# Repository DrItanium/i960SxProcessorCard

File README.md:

A 4-layer PCB meant to break the control signals of an i960Sx processor in the
form of an Arduino Mega 2560 shield. I designed this board to make sure that I
would not have to continually make 4-layer boards on multiple screw ups.

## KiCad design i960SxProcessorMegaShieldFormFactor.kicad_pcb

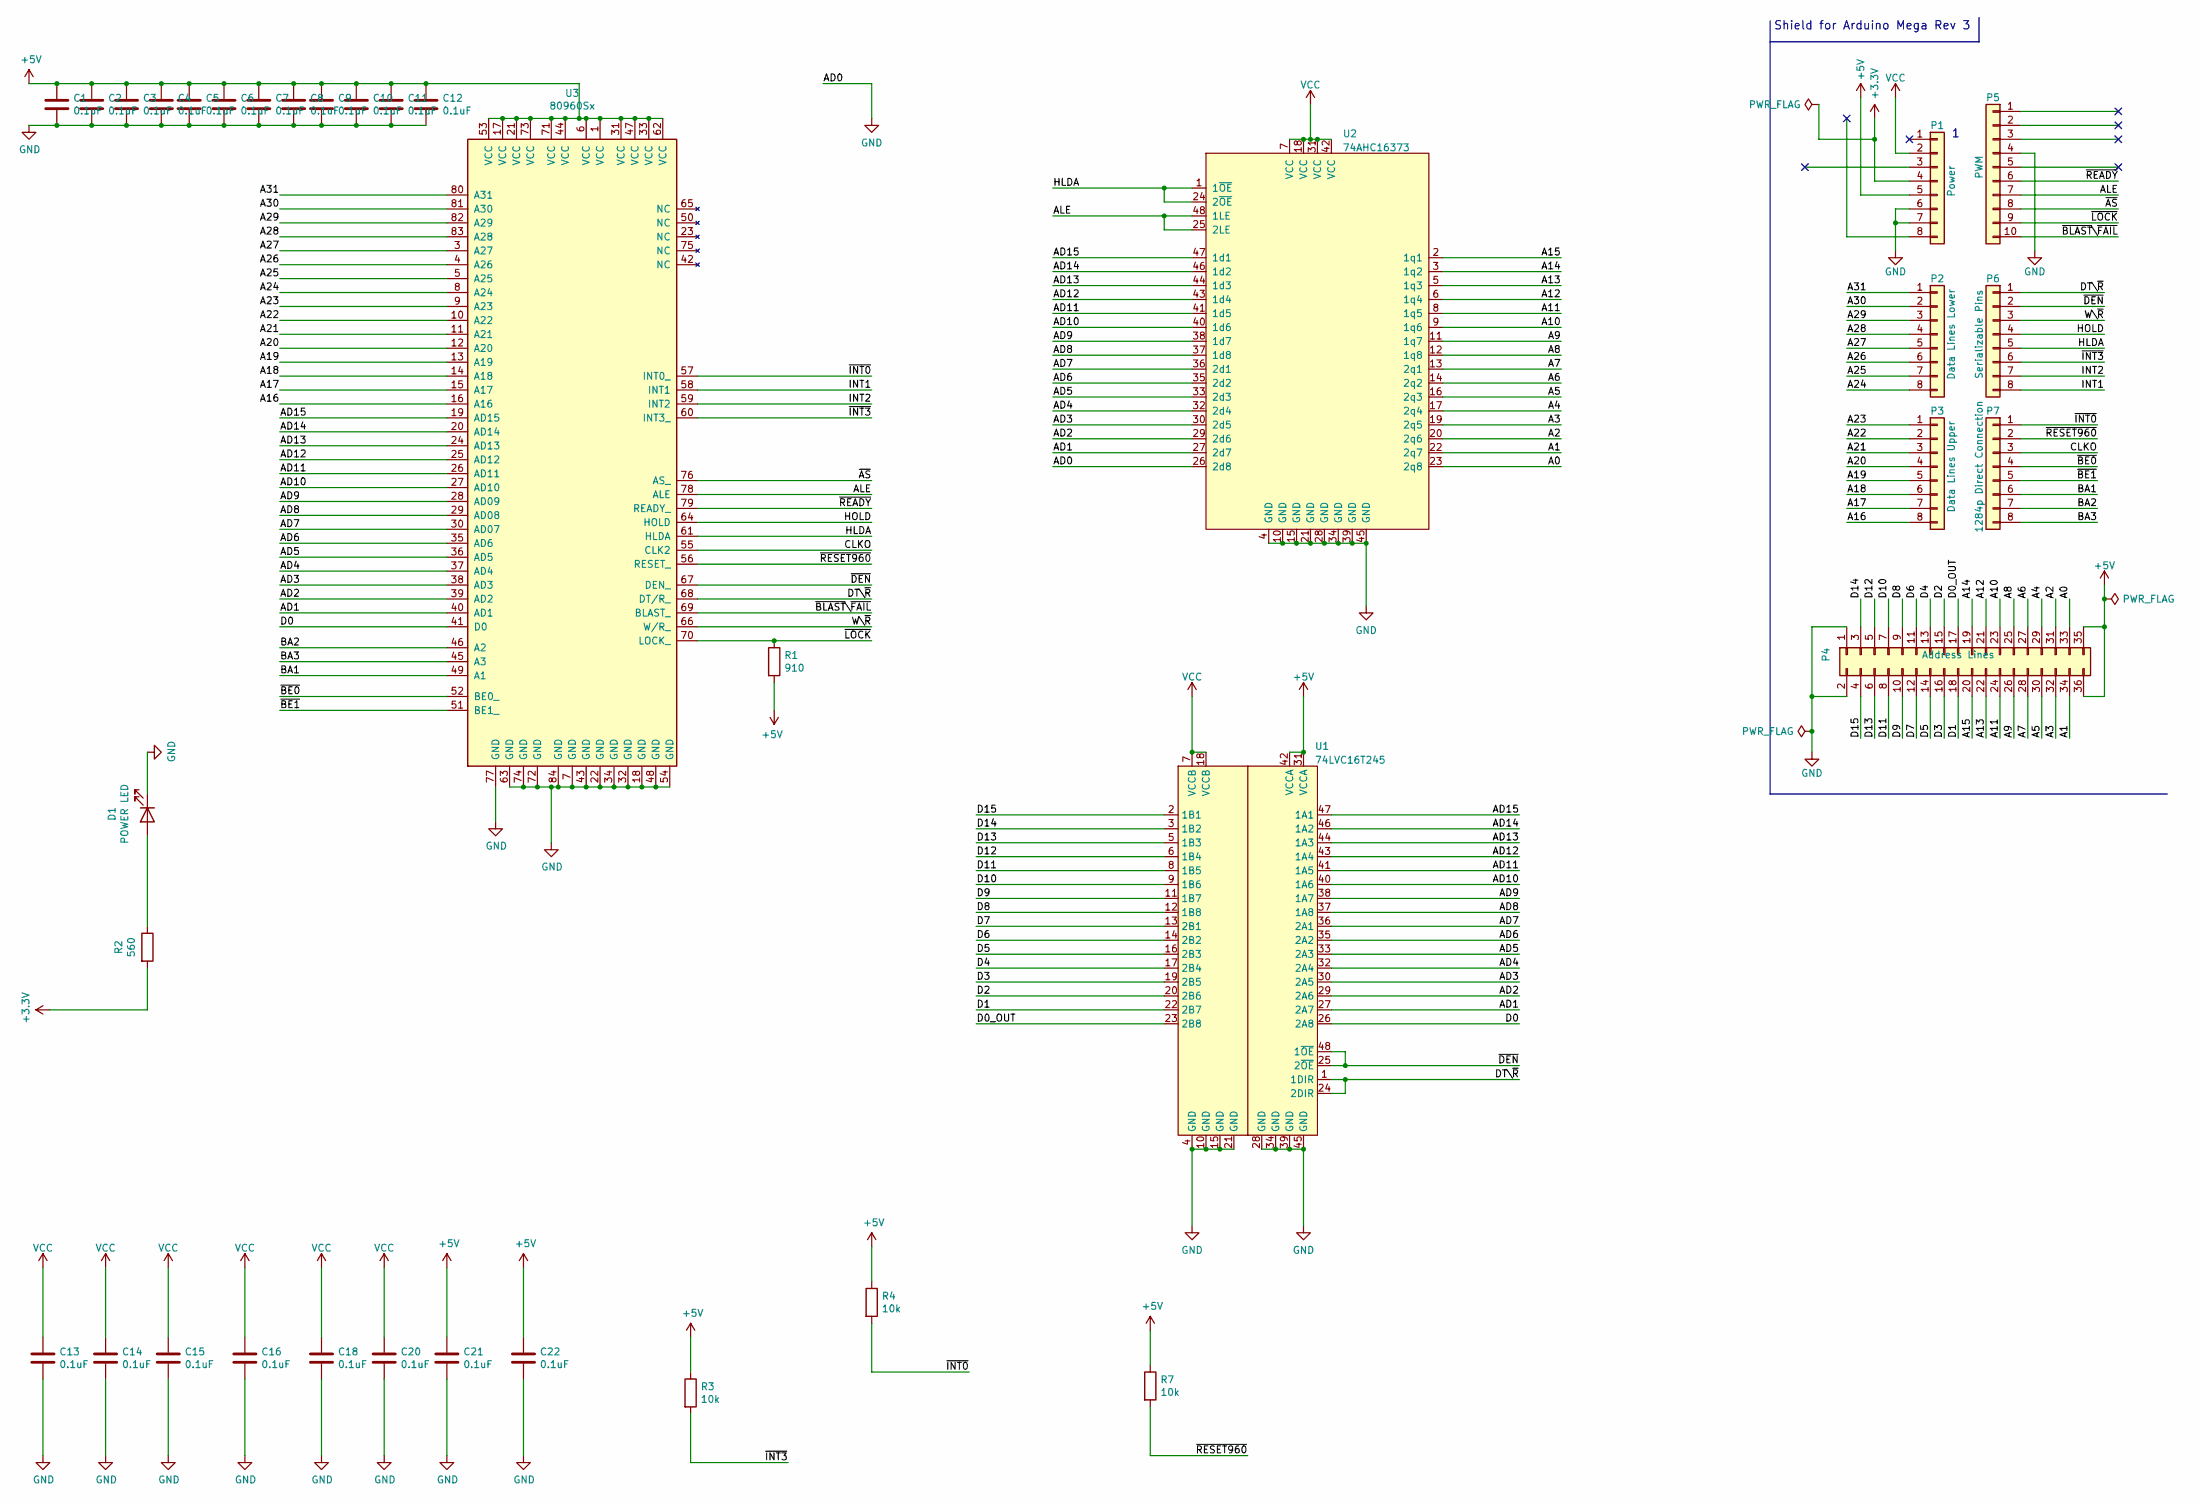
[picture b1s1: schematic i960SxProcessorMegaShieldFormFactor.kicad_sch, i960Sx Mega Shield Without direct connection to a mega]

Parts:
C1, C2, C3, C4, C5, C6, C7, C8, C9, C10, C11, C12, C13, C14, C15, C16, C18, C20, C21, C22: 0.1uF; C_0805_2012Metric_Pad1.18x1.45mm_HandSolder
D1: POWER LED; LED_0805_2012Metric
P1: Power; Socket_Strip_Arduino_1x08
P2: Data Lines Lower; Socket_Strip_Arduino_1x08
P3: Data Lines Upper; Socket_Strip_Arduino_1x08
P4: Address Lines; Socket_Strip_Arduino_2x18
P5: PWM; Socket_Strip_Arduino_1x10
P6: Serializable Pins; Socket_Strip_Arduino_1x08
P7: 1284p Direct Connection; Socket_Strip_Arduino_1x08
R1: 910; R_0805_2012Metric_Pad1.20x1.40mm_HandSolder
R2: 560; R_0805_2012Metric_Pad1.20x1.40mm_HandSolder
R3, R4, R7: 10k; R_0805_2012Metric_Pad1.20x1.40mm_HandSolder
U1: 74LVC16T245; TSSOP-48_6.1x12.5mm_P0.5mm
U2: 74AHC16373; TSSOP-48_6.1x12.5mm_P0.5mm
U3: 80960Sx; PLCC-84_THT-Socket

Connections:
+3V3: P1.4, R2.2
+5V: C1.1, C2.1, C3.1, C4.1, C5.1, C6.1, C7.1, C8.1, C9.1, C10.1, C11.1, C12.1, C21.1, C22.1, P1.5, P4.35, P4.36, R1.2, R3.1, R4.1, R7.1, U1.31 (VCCA), U1.42 (VCCA), U3.1 (VCC), U3.6 (VCC), U3.17 (VCC), U3.21 (VCC), U3.31 (VCC), U3.33 (VCC), U3.44 (VCC), U3.47 (VCC), U3.53 (VCC), U3.62 (VCC), U3.71 (VCC), U3.73 (VCC)
/A0: P4.33, U2.23 (2q8)
/A1: P4.34, U2.22 (2q7)
/A2: P4.31, U2.20 (2q6)
/A3: P4.32, U2.19 (2q5)
/A4: P4.29, U2.17 (2q4)
/A5: P4.30, U2.16 (2q3)
/A6: P4.27, U2.14 (2q2)
/A7: P4.28, U2.13 (2q1)
/A8: P4.25, U2.12 (1q8)
/A9: P4.26, U2.11 (1q7)
/A10: P4.23, U2.9 (1q6)
/A11: P4.24, U2.8 (1q5)
/A12: P4.21, U2.6 (1q4)
/A13: P4.22, U2.5 (1q3)
/A14: P4.19, U2.3 (1q2)
/A15: P4.20, U2.2 (1q1)
/A16: P3.8, U3.16 (A16)
/A17: P3.7, U3.15 (A17)
/A18: P3.6, U3.14 (A18)
/A19: P3.5, U3.13 (A19)
/A20: P3.4, U3.12 (A20)
/A21: P3.3, U3.11 (A21)
/A22: P3.2, U3.10 (A22)
/A23: P3.1, U3.9 (A23)
/A24: P2.8, U3.8 (A24)
/A25: P2.7, U3.5 (A25)
/A26: P2.6, U3.4 (A26)
/A27: P2.5, U3.3 (A27)
/A28: P2.4, U3.83 (A28)
/A29: P2.3, U3.82 (A29)
/A30: P2.2, U3.81 (A30)
/A31: P2.1, U3.80 (A31)
/AD1: U1.27 (2A7), U2.27 (2d7), U3.40 (AD1)
/AD2: U1.29 (2A6), U2.29 (2d6), U3.39 (AD2)
/AD3: U1.30 (2A5), U2.30 (2d5), U3.38 (AD3)
/AD4: U1.32 (2A4), U2.32 (2d4), U3.37 (AD4)
/AD5: U1.33 (2A3), U2.33 (2d3), U3.36 (AD5)
/AD6: U1.35 (2A2), U2.35 (2d2), U3.35 (AD6)
/AD7: U1.36 (2A1), U2.36 (2d1), U3.30 (AD07)
/AD8: U1.37 (1A8), U2.37 (1d8), U3.29 (AD08)
/AD9: U1.38 (1A7), U2.38 (1d7), U3.28 (AD09)
/AD10: U1.40 (1A6), U2.40 (1d6), U3.27 (AD10)
/AD11: U1.41 (1A5), U2.41 (1d5), U3.26 (AD11)
/AD12: U1.43 (1A4), U2.43 (1d4), U3.25 (AD12)
/AD13: U1.44 (1A3), U2.44 (1d3), U3.24 (AD13)
/AD14: U1.46 (1A2), U2.46 (1d2), U3.20 (AD14)
/AD15: U1.47 (1A1), U2.47 (1d1), U3.19 (AD15)
/ALE: P5.7, U2.25 (2LE), U2.48 (1LE), U3.78 (ALE)
/BA1: P7.6, U3.49 (A1)
/BA2: P7.7, U3.46 (A2)
/BA3: P7.8, U3.45 (A3)
/CLKO: P7.3, U3.55 (CLK2)
/D0: U1.26 (2A8), U3.41 (D0)
/D0_OUT: P4.17, U1.23 (2B8)
/D1: P4.18, U1.22 (2B7)
/D2: P4.15, U1.20 (2B6)
/D3: P4.16, U1.19 (2B5)
/D4: P4.13, U1.17 (2B4)
/D5: P4.14, U1.16 (2B3)
/D6: P4.11, U1.14 (2B2)
/D7: P4.12, U1.13 (2B1)
/D8: P4.9, U1.12 (1B8)
/D9: P4.10, U1.11 (1B7)
/D10: P4.7, U1.9 (1B6)
/D11: P4.8, U1.8 (1B5)
/D12: P4.5, U1.6 (1B4)
/D13: P4.6, U1.5 (1B3)
/D14: P4.3, U1.3 (1B2)
/D15: P4.4, U1.2 (1B1)
/DT\~R: P6.1, U1.1 (1DIR), U1.24 (2DIR), U3.68 (DT/R_)
/HLDA: P6.5, U2.1 (1~OE), U2.24 (2~OE), U3.61 (HLDA)
/HOLD: P6.4, U3.64 (HOLD)
/INT1: P6.8, U3.58 (INT1)
/INT2: P6.7, U3.59 (INT2)
/W\~R: P6.3, U3.66 (W/R_)
/~AS: P5.8, U3.76 (AS_)
/~BE0: P7.4, U3.52 (BE0_)
/~BE1: P7.5, U3.51 (BE1_)
/~BLAST\~FAIL: P5.10, U3.69 (BLAST_)
/~DEN: P6.2, U1.25 (2~OE), U1.48 (1~OE), U3.67 (DEN_)
/~INT0: P7.1, R4.2, U3.57 (INT0_)
/~INT3: P6.6, R3.2, U3.60 (INT3_)
/~LOCK: P5.9, R1.1, U3.70 (LOCK_)
/~READY: P5.6, U3.79 (READY_)
/~RESET960: P7.2, R7.2, U3.56 (RESET_)
GND: C1.2, C2.2, C3.2, C4.2, C5.2, C6.2, C7.2, C8.2, C9.2, C10.2, C11.2, C12.2, C13.2, C14.2, C15.2, C16.2, C18.2, C20.2, C21.2, C22.2, D1.1 (K), P1.6, P1.7, P4.1, P4.2, P5.4, U1.4 (GND), U1.10 (GND), U1.15 (GND), U1.21 (GND), U1.28 (GND), U1.34 (GND), U1.39 (GND), U1.45 (GND), U2.4 (GND), U2.10 (GND), U2.15 (GND), U2.21 (GND), U2.26 (2d8), U2.28 (GND), U2.34 (GND), U2.39 (GND), U2.45 (GND), U3.7 (GND), U3.18 (GND), U3.22 (GND), U3.32 (GND), U3.34 (GND), U3.43 (GND), U3.48 (GND), U3.54 (GND), U3.63 (GND), U3.72 (GND), U3.74 (GND), U3.77 (GND), U3.84 (GND)
unnamed: D1.2 (A), R2.1
VCC: C13.1, C14.1, C15.1, C16.1, C18.1, C20.1, P1.2, U1.7 (VCCB), U1.18 (VCCB), U2.7 (VCC), U2.18 (VCC), U2.31 (VCC), U2.42 (VCC)

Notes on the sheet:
Shield for Arduino Mega Rev 3

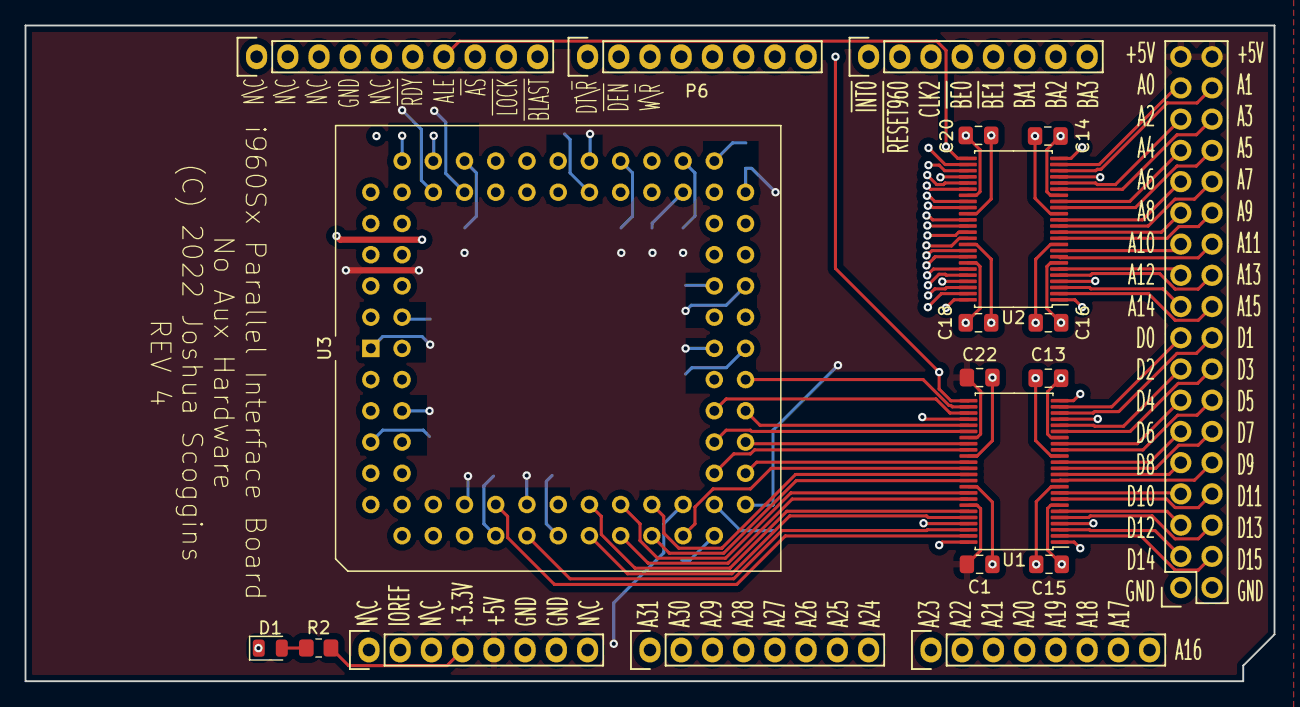
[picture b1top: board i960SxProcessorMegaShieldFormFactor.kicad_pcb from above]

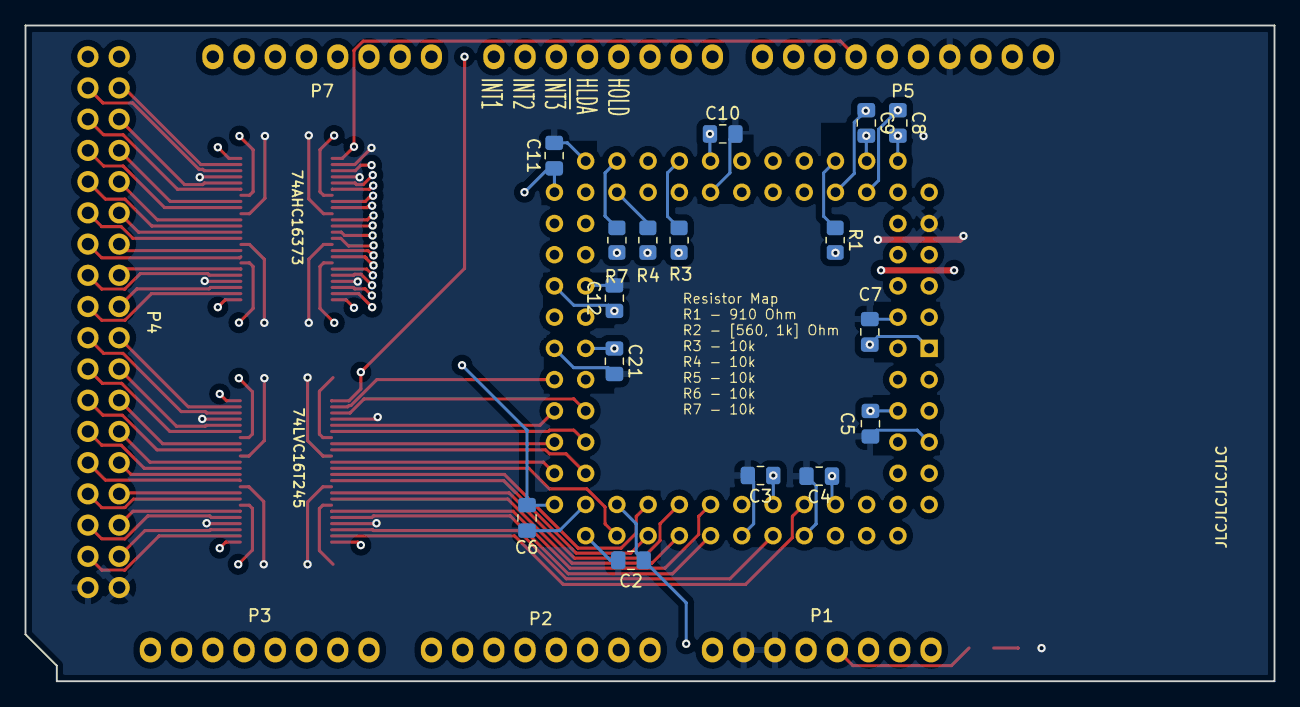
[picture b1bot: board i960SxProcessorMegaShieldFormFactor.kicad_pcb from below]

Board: 4 copper layers, 101.6 x 53.3 mm, 36 parts (16 on the bottom side), 90 nets.

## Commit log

2021-10-21 Initial rev 1 commit
2021-10-21 Added the CC-BY-SA 4 license
2021-10-21 Added CC-BY-SA silk screen
2021-10-21 Added a readme
2021-10-21 link up pre-existing external hardware
    Fix errors and make sure we are using AHC parts
2021-10-21 Start placing different ics
2021-10-21 Rearrange some connections and try to shove the aux hardware closer together
2021-10-21 Move the transceivers and registers to make room for the aux hardware
2021-10-21 Mostly complete rewiring
2021-10-21 Save the added pullup resistor
2021-10-21 Finish wiring the last two non power pins
2021-10-21 added a track for the 3.3v power led
2021-10-21 Finished initial design
    Still need to update the silk screens
2021-10-21 Put the data and address lines back into the previous design
    Maximizes compatibility?
2021-10-21 Fix labeling
2021-10-21 Rearrange aux hardware to reduce via count
    Start routing the rest of the traces out of the i960
2021-10-21 Finished non power routing
2021-10-21 Power routing done?
2021-10-21 Added documentation text
2021-10-21 Text addons done
2021-10-21 Add missing labelling
2021-10-21 expose clock signal div 2
2021-10-21 connect 10mhz clock to compatible output pin
2021-10-21 Connect MCU_RDY to ~READY pin
    In the old designs, the ~READY pin was never used outside of the stack
    and the ~MCU_RDY pin was used in its place. I want to now make it so
    that using ~READY will always be synchronized. But the older rev1 cards
    directly connect ready to the i960Sx
2021-10-21 Make sure we connect ~MCU_RDY to ~READY to make the design backwards compatible
    I can reuse the two stack version of the processor card interface in
    future designs as well.
2021-10-21 Make sure...
2022-11-12 More fix up actions
2022-11-12 ExternalHardware added
2022-11-12 Use a GAL chip to consolidate the number of chips
    I have many extra free entries on the GAL to assist me in doing stuff
2022-11-12 Whoops, missing the kicad 6 files :/
2022-11-13 Use PLCC20 for the GAL chip instead of the much larger DIP20
2022-11-13 Introduce the 74LVC16T245 for the datalines
2022-11-13 Just do the consolidation
2022-11-13 Finished retracing
2022-11-13 Update tags and add GAL16V8 script
2022-11-13 Finished initial design
2022-12-08 Remove a resistor and drop the 10MHz output clock
2022-12-08 Broke the link
2022-12-08 Remove the external hardware sheet
    We want to keep this board as simple as possible
    Having the extra signal setups is not a smart move it seems
2022-12-08 Clean up all of the aux hardware and put the capacitors in the area underneath the socket
    It makes it much cleaner
    Also, I made sure that the ground and power planes are on all layers to
    reduce complexity
2022-12-08 set active layer
2022-12-09 Finished wiring
    Super easy this way :)
2022-12-09 Finished the new implementation
2022-12-09 gerber files

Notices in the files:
i960SxProcessorMegaShieldFormFactor.kicad_pcb:
(C) 2022 Joshua Scoggins
